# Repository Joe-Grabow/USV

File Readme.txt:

Development branch for IMU - Xiaotian Zhai

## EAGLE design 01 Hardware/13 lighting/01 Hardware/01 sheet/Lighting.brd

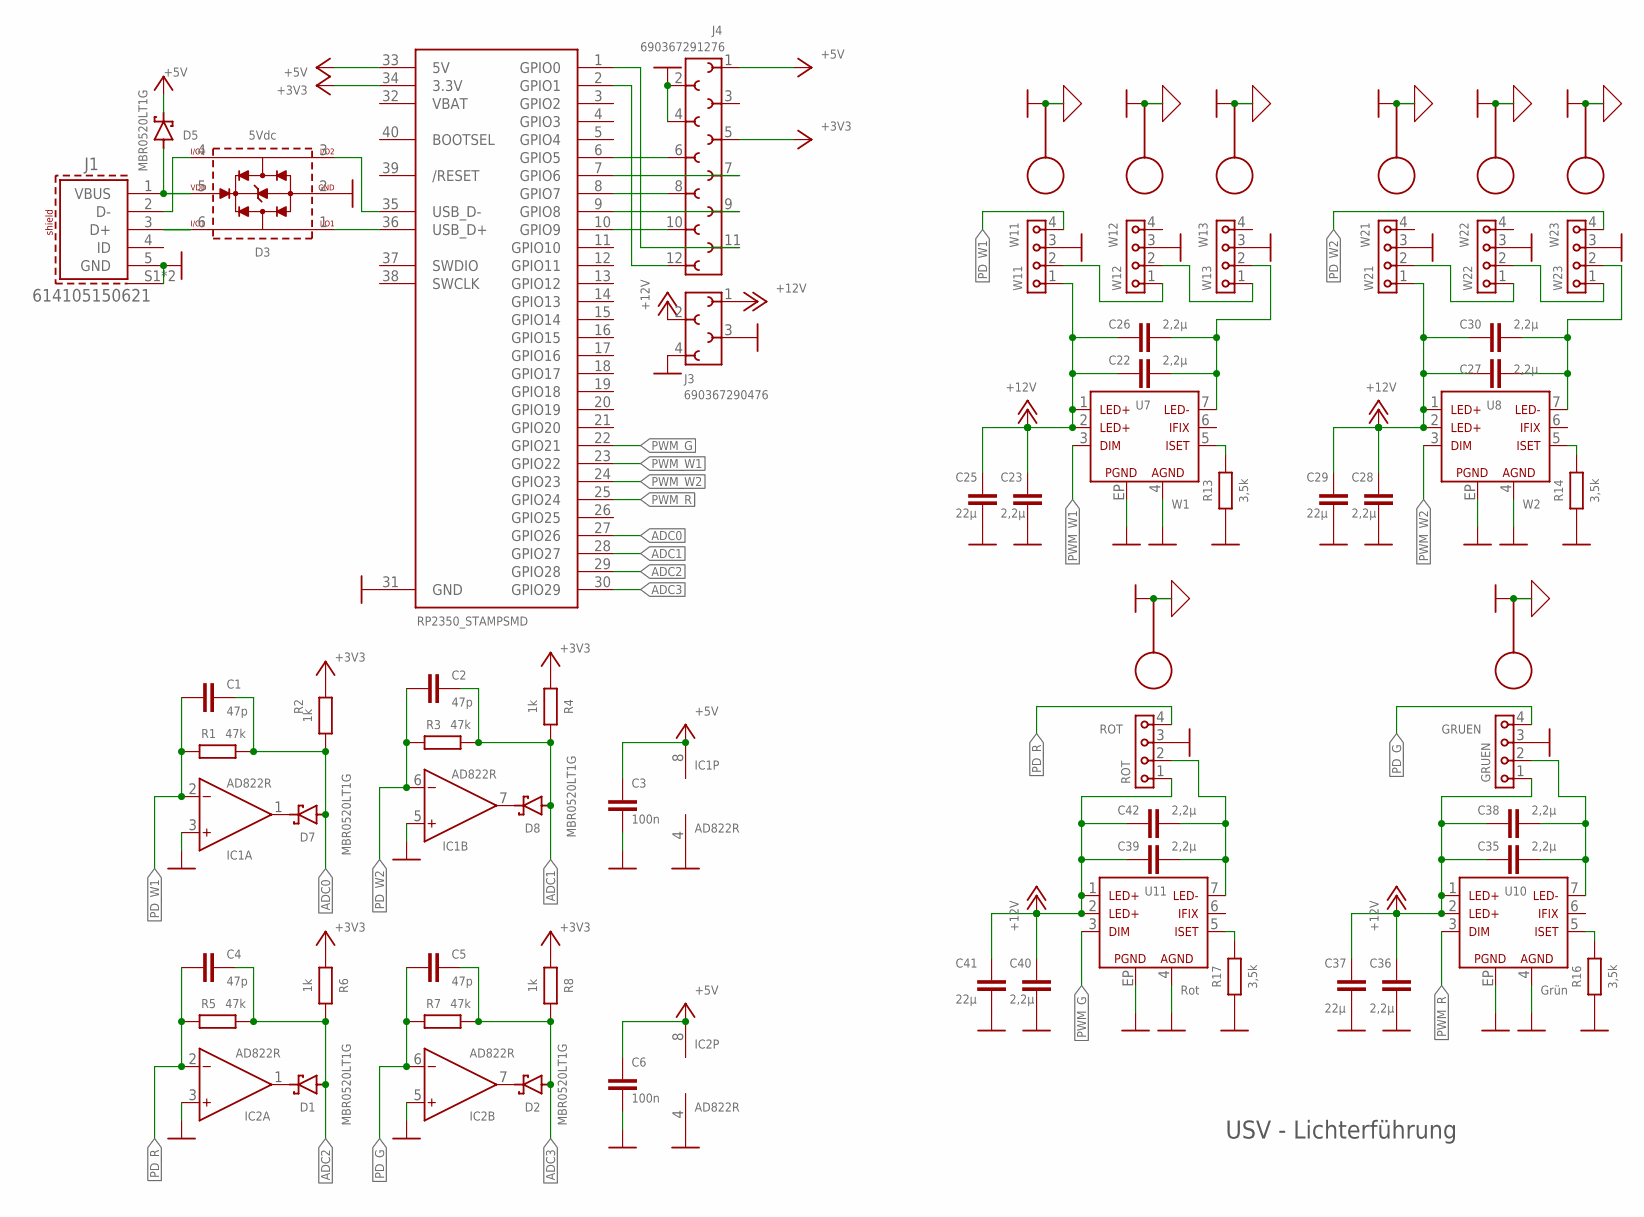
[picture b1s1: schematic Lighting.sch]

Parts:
C1, C2, C4, C5: 47p; CAPC2012X110
C3, C6: 100n; CAPC2012X110
C22, C23, C26, C27, C28, C30, C35, C36, C38, C39, C40, C42: 2,2µ; CAPC2012X110
C25, C29, C37, C41: 22µ; CAPC2012X110
D1, D2, D5, D7, D8: MBR0520LT1G; SODFL3718X115
D3: 5Vdc; WE-TVS_SOT563
GRUEN: GRUEN; LED_PLATINE
IC1, IC2: AD822R; SO8
J1: 614105150621
J3: 690367290476
J4: 690367291276
R1, R3, R5, R7: 47k; RESC2012X65
R2, R4, R6, R8: 1k; RESC2012X65
R13, R14, R16, R17: 3,5k; RESC2012X65
ROT: ROT; LED_PLATINE
U7: W1; MAGI³C-LDHM_172946001
U8: W2; MAGI³C-LDHM_172946001
U10: Grün; MAGI³C-LDHM_172946001
U11: Rot; MAGI³C-LDHM_172946001
U$1: RP2350_STAMPSMD; RP2XXX_STAMP_SMD
W11: W11; LED_PLATINE
W12: W12; LED_PLATINE
W13: W13; LED_PLATINE
W21: W21; LED_PLATINE
W22: W22; LED_PLATINE
W23: W23; LED_PLATINE

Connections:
+3V3: J4.5, R2.2, R4.2, R6.2, R8.2, U$1.34 (3.3V)
+5V: C3.1, C6.1, D5.1 (C), IC1.8 (V+), IC2.8 (V+), J4.1, U$1.33 (5V)
+12V: C22.1, C23.1, C25.1, C26.1, C27.1, C28.1, C29.1, C30.1, C35.1, C36.1, C37.1, C38.1, C39.1, C40.1, C41.1, C42.1, GRUEN.1, J3.1, J3.2, ROT.1, U7.1 (LED+), U7.2 (LED1+), U8.1 (LED+), U8.2 (LED1+), U10.1 (LED+), U10.2 (LED1+), U11.1 (LED+), U11.2 (LED1+), W11.1, W21.1
ADC0: C1.2, D7.2 (A), R1.1, R2.1, U$1.27 (GPIO26)
ADC1: C2.2, D8.2 (A), R3.1, R4.1, U$1.28 (GPIO27)
ADC2: C4.2, D1.2 (A), R5.1, R6.1, U$1.29 (GPIO28)
ADC3: C5.2, D2.2 (A), R7.1, R8.1, U$1.30 (GPIO29)
D+@1: D3.6 (I/O3), J1.3 (D+)
D-@1: D3.4 (I/O4), J1.2 (D-)
D_N: D3.3 (I/O2), U$1.35 (USB_D-)
D_P: D3.1 (I/O1), U$1.36 (USB_D+)
GND: C3.2, C6.2, C23.2, C25.2, C28.2, C29.2, C36.2, C37.2, C40.2, C41.2, D3.2 (GND), GRUEN.3, GRUEN.5, IC1.3 (IN+), IC1.4 (V-), IC1.5 (IN+), IC2.3 (IN+), IC2.4 (V-), IC2.5 (IN+), J1.5 (GND), J1.S1 (SHIELD), J1.S2 (SHIELD), J3.3, J3.4, J4.2, J4.4, R13.1, R14.1, R16.1, R17.1, ROT.3, ROT.5, U7.4 (AGND), U7.EP (PGND), U8.4 (AGND), U8.EP (PGND), U10.4 (AGND), U10.EP (PGND), U11.4 (AGND), U11.EP (PGND), U$1.31 (GND), W11.3, W11.5, W12.3, W12.5, W13.3, W13.5, W21.3, W21.5, W22.3, W22.5, W23.3, W23.5
LED-G-: C35.2, C38.2, GRUEN.2, U10.7 (LED-)
LED-R-: C39.2, C42.2, ROT.2, U11.7 (LED-)
LED-W1-: C22.2, C26.2, U7.7 (LED-), W13.2
LED_W2-: C27.2, C30.2, U8.7 (LED-), W23.2
unnamed: D1.1 (C), IC2.1 (OUT)
unnamed: D2.1 (C), IC2.7 (OUT)
unnamed: J4.10, U$1.10 (GPIO9)
unnamed: D7.1 (C), IC1.1 (OUT)
unnamed: J4.9, U$1.9 (GPIO8)
unnamed: J4.8, U$1.8 (GPIO7)
unnamed: J4.7, U$1.7 (GPIO6)
unnamed: D8.1 (C), IC1.7 (OUT)
unnamed: J4.6, U$1.6 (GPIO5)
unnamed: R16.2, U10.5 (ISET)
unnamed: R17.2, U11.5 (ISET)
unnamed: R13.2, U7.5 (ISET)
unnamed: J4.12, U$1.2 (GPIO1)
unnamed: J4.11, U$1.1 (GPIO0)
unnamed: R14.2, U8.5 (ISET)
PD_G: C5.1, GRUEN.4, IC2.6 (IN-), R7.2
PD_R: C4.1, IC2.2 (IN-), R5.2, ROT.4
PD_W1: C1.1, IC1.2 (IN-), R1.2, W11.4
PD_W2: C2.1, IC1.6 (IN-), R3.2, W23.4
PWM_G: U11.3 (DIM), U$1.22 (GPIO21)
PWM_R: U10.3 (DIM), U$1.25 (GPIO24)
PWM_W1: U7.3 (DIM), U$1.23 (GPIO22)
PWM_W2: U8.3 (DIM), U$1.24 (GPIO23)
VBAT: U$1.32 (VBAT)
VBUS: D3.5 (VDD), D5.2 (A), J1.1 (VBUS)
W11_W12: W11.2, W12.1
W12_W13: W12.2, W13.1
W21_W22: W21.2, W22.1
W22_W23: W22.2, W23.1

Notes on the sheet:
USV - Lichterführung

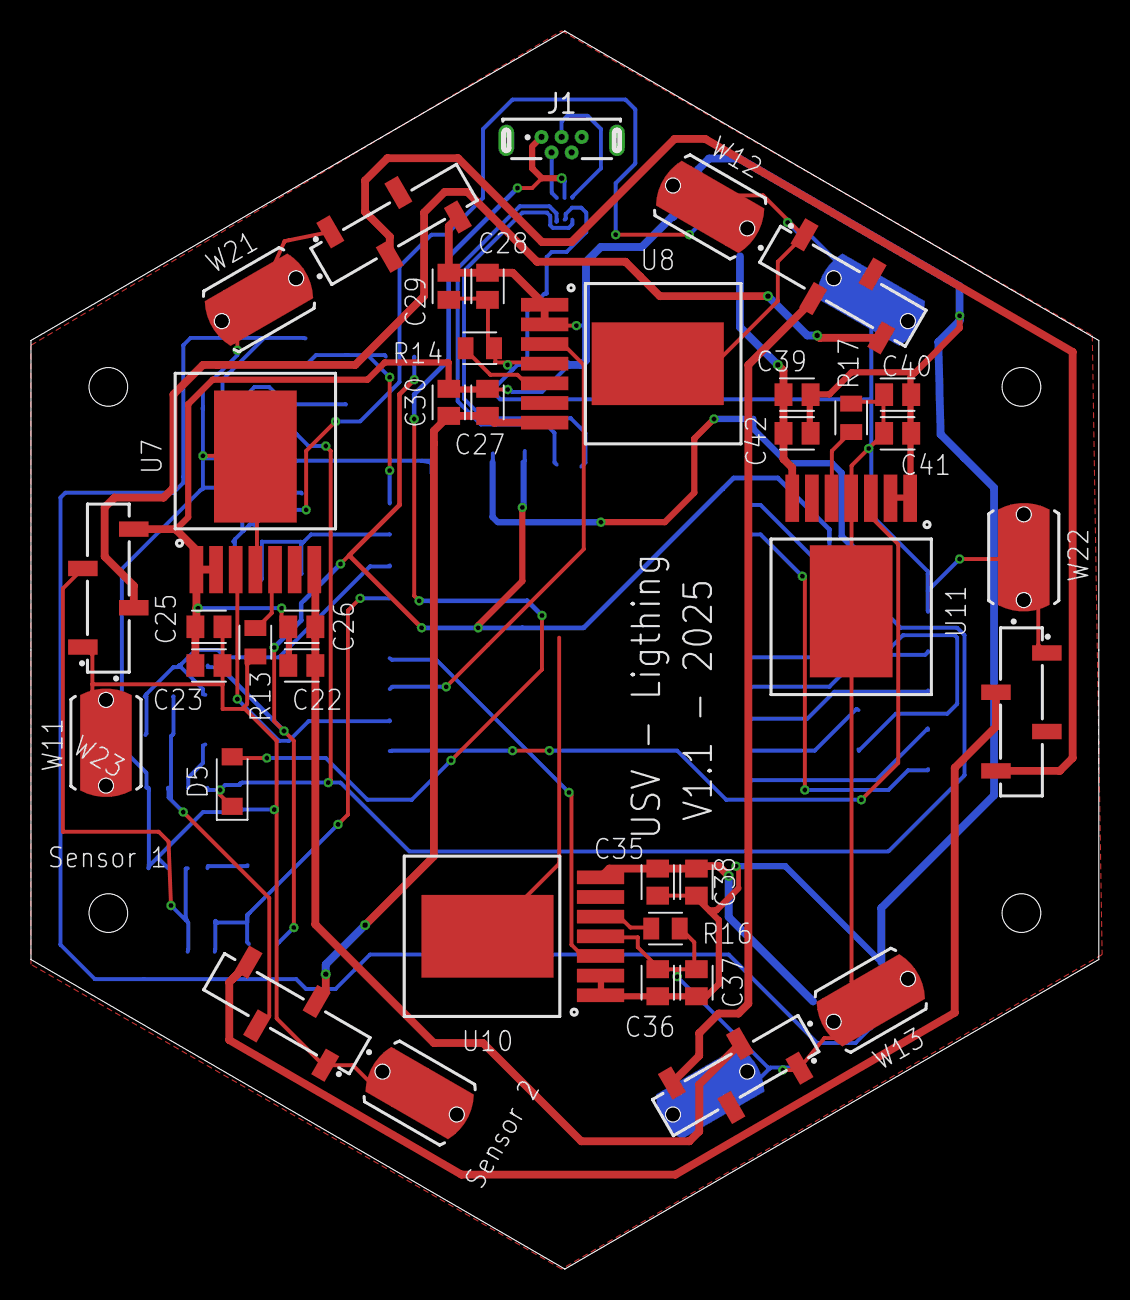
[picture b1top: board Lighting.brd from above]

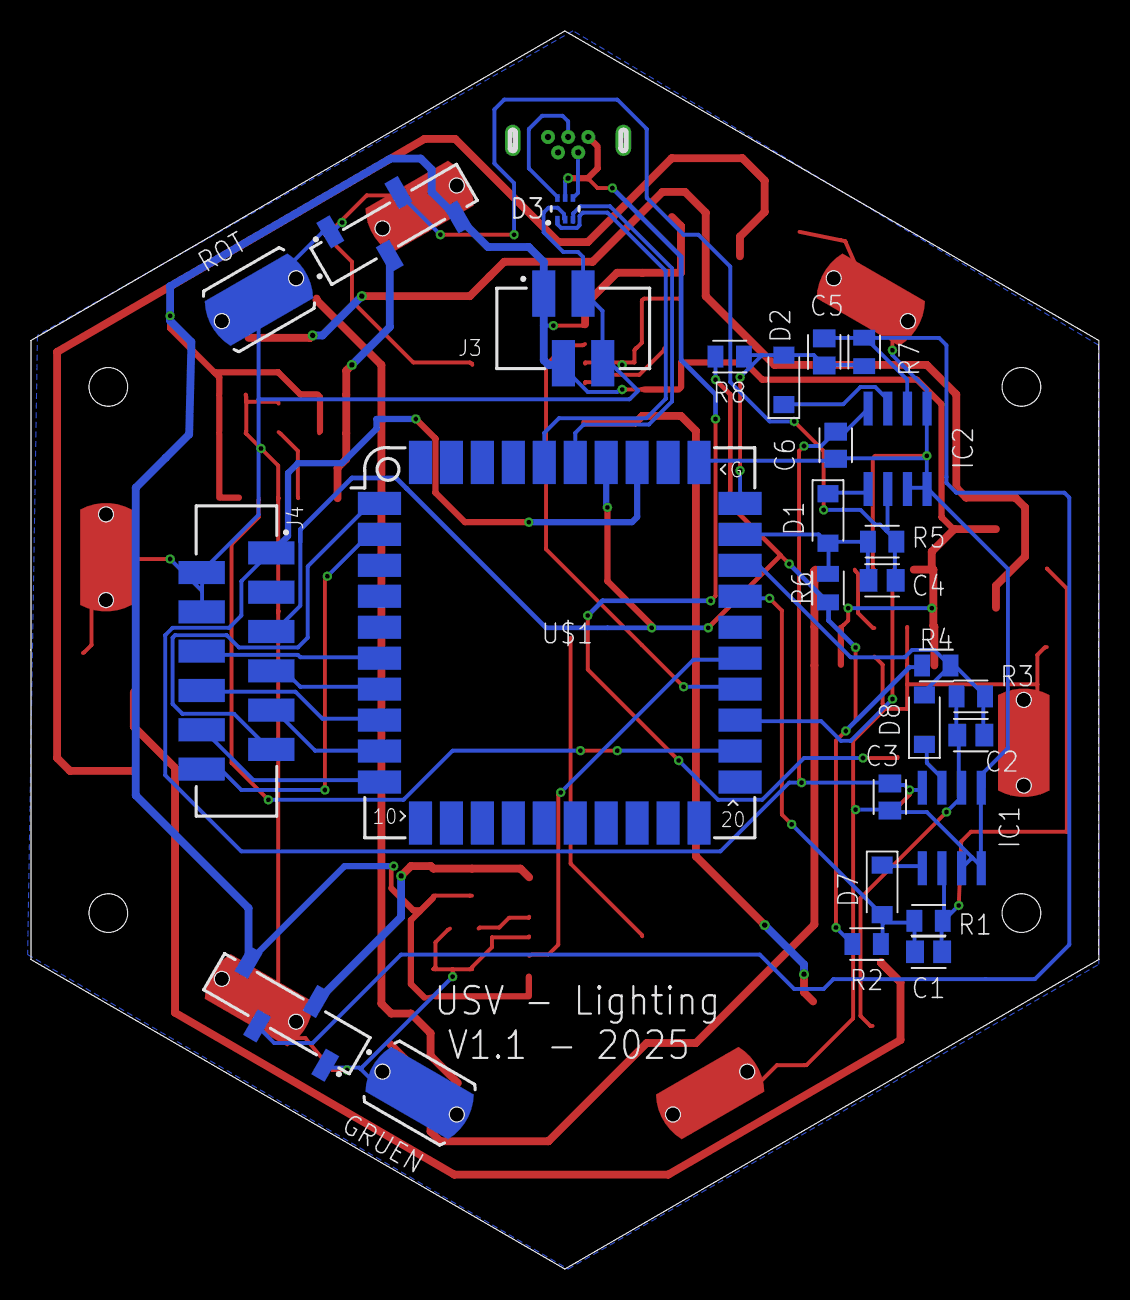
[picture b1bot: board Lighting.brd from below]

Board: 2 copper layers, 68.7 x 79.7 mm, 58 parts (26 on the bottom side), 44 nets.

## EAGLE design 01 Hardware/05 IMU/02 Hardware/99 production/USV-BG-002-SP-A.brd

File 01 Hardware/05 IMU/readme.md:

## Slave für die inertiale Messeinheit (IMU).
Messung und räumliche Kombination mehrerer Inertialsensoren.

Messgrößen sind:
- Beschleunigung in x, y, z
- Drehraten in x, y, z
- Magnetometerdaten in x, y, z

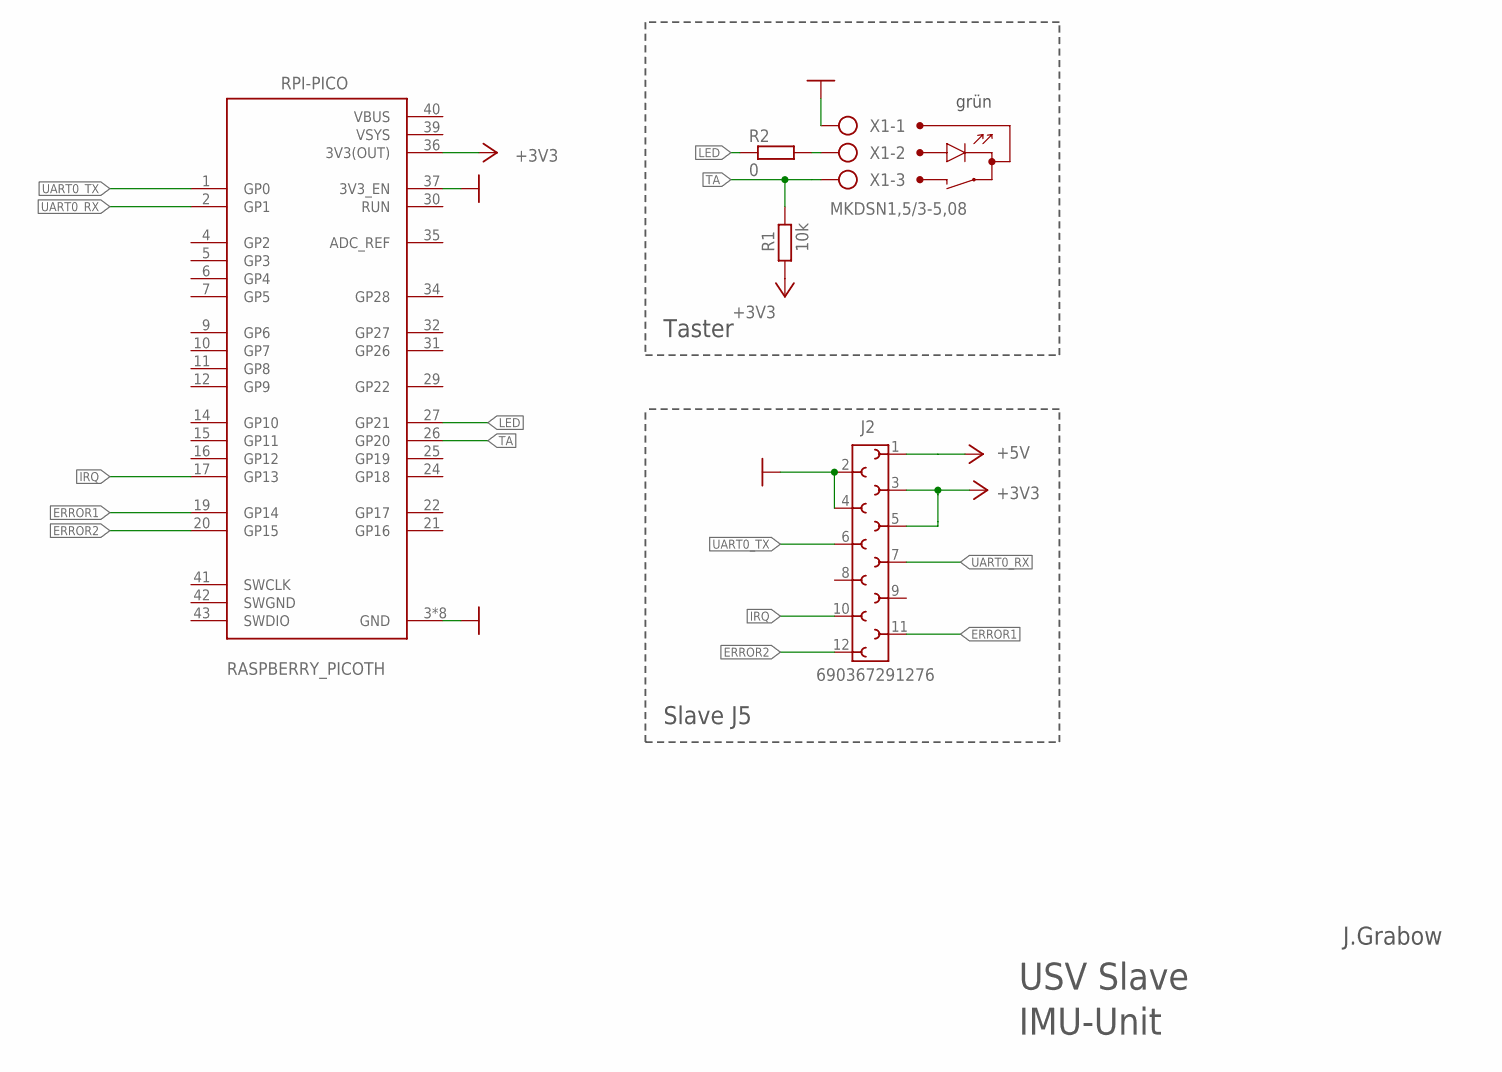
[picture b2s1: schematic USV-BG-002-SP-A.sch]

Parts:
J2: 690367291276
R1: 10k; M0805
R2: 0; R0805
RPI-PICO: RASPBERRY_PICOTH; PICO-PKG-TH
X1: MKDSN1,5/3-5,08

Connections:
+3V3: J2.3, J2.5, R1.1, RPI-PICO.36 (3V3(OUT))
+5V: J2.1
ERROR1: J2.11, RPI-PICO.19 (GP14)
ERROR2: J2.12, RPI-PICO.20 (GP15)
GND: J2.2, J2.4, RPI-PICO.3 (GND), RPI-PICO.8 (GND), RPI-PICO.13 (GND), RPI-PICO.18 (GND), RPI-PICO.23 (GND), RPI-PICO.28 (GND), RPI-PICO.33 (GND), RPI-PICO.37 (3V3_EN), RPI-PICO.38 (GND), X1.1
IRQ: J2.10, RPI-PICO.17 (GP13)
LED: R2.1, RPI-PICO.27 (GP21)
LED/IO2A: R2.2, X1.2
SWGND: RPI-PICO.42 (SWGND)
TA: R1.2, RPI-PICO.26 (GP20), X1.3
UART0_RX: J2.7, RPI-PICO.2 (GP1)
UART0_TX: J2.6, RPI-PICO.1 (GP0)
VBUS: RPI-PICO.40 (VBUS)
VSYS: RPI-PICO.39 (VSYS)

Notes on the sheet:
Taster
IMU-Unit
USV Slave
J.Grabow
Slave J5
grün

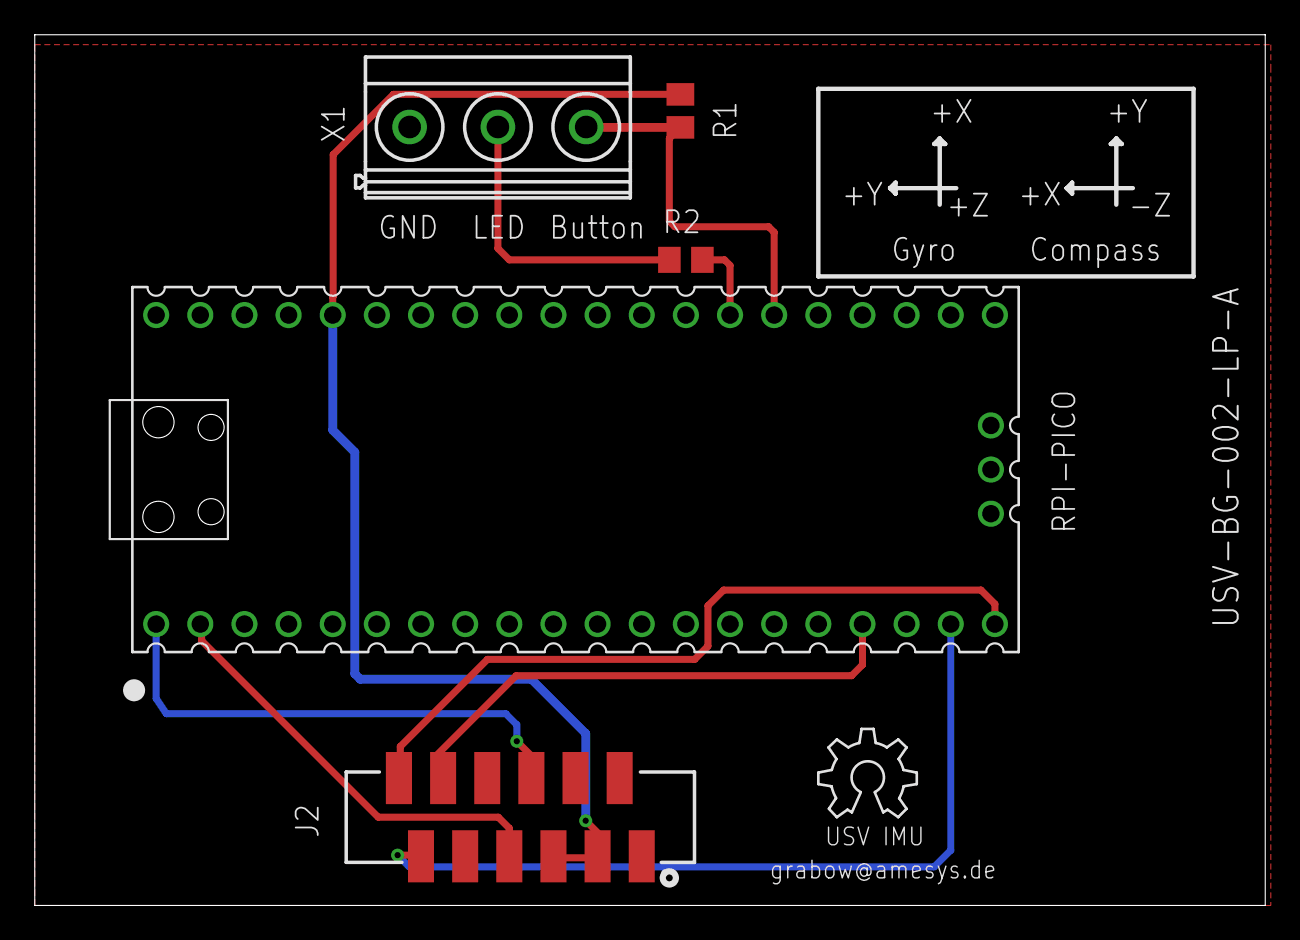
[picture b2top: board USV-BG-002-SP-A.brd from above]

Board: 2 copper layers, 70.8 x 50.1 mm, 6 parts (0 on the bottom side), 10 nets.

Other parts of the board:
U$1: OSHW_6X200_NOTEXT

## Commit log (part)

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2023-07-13 Tab.5 Byte-Index korrigiert zu (6 … n+5)
2023-11-07 Initiale Erstellung des Unterordners
2023-11-09 Nummerierung angepasst
2023-11-13 Initiale Erstellung
2023-11-25 Development branch for IMU - C. Roepke
2023-11-25 Software-Programm, um mit externen Taster, dazugehörigen Pullup-Widerstand sowie Taster-Entprellung die LED des kap. Taster ein- und auszuschalten
2023-11-30 hier wird die Sensorfusion bearbeitet.
2023-12-02 Change in program line 21: Triggering on falling edge instead of rising edge
2023-12-02 Imported "picozero" library into "Test_Button.py" and adapted program code accordingly
2023-12-20 testen, ob LED (onboard) funktioniert
2024-01-15 - Datenblatt MPU_9250 Registermap und Datenblatt AK8963 - erster Entwurf State-Machine IMU + Dokumentation
2024-03-05 - Sensordaten (Beschleunigung, Gyroskop, Magnet, Temperatur) werden über UART empfangen und ausgelesen - Thread erstellt, da kein IRQ für UART implementiert ist - Thread besteht aus zwei Teilen (Teil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
2024-03-08 - Funktion zum Drehen der Koordinatenachsen vom Gyro-, Beschleunigungs- und Magnetsensor in das Schiffskoordinatensystem - getestet
2024-03-08 - Definition einer Datenklasse für Zeit-, Beschleunigungs-, Gyro-, Magnet- und Temperaturdaten des MPU9250
2024-03-08 - Empfangen und Auslesen von MPU9250 Sensordaten
2024-03-11 - Version 1 überarbeitet
2024-03-12 - Version 1.2 - globale Variablen (bis auf Timer) in eine extra Klasse ausgelagert - state Machine für Thread 1 implementiert und ausgelagert
2024-03-12 - Erstellung einer extra Klasse für Flags, um globale Variablen zu umgehen
2024-03-12 - Erstellung und Auslagerung einer state Machine für Thread 1
2024-03-19 - Erweiterung der MPU9250 Datenklasse um die Funktion def copy() - def copy() integriert, um Daten innerhalb der state Machine nicht zu überschreiben
2024-03-19 - Erweiterung des Kalibrierskripts um die Funktion def check_cal_data() - calibration_routine_ak8963() als Klasse definiert (Kalibrierung noch nicht funktionsfähig)
2024-03-19 - Thread1_StateMachine als Klasse definiert und die Funktion def StateMachine erweitert
2024-03-21 - Erweiterung state Machine
2024-03-21 - Version 1.2 - Funktionen def findPerAndCalc(), def cal() and def valueCorrect() hinzugefügt - Kalibrierung (Ellipse) getestet und funktionsfähig
2025-12-02 new Lighting PCB
2026-03-02 new Pinlayout (LED-Board)
2026-04-24 07 drive: Hardware and Software added
    07 drive: Hardware and Software added

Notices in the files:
parts and their libraries:
Eagle_WR-MM: Copyright: Würth Elektronik
